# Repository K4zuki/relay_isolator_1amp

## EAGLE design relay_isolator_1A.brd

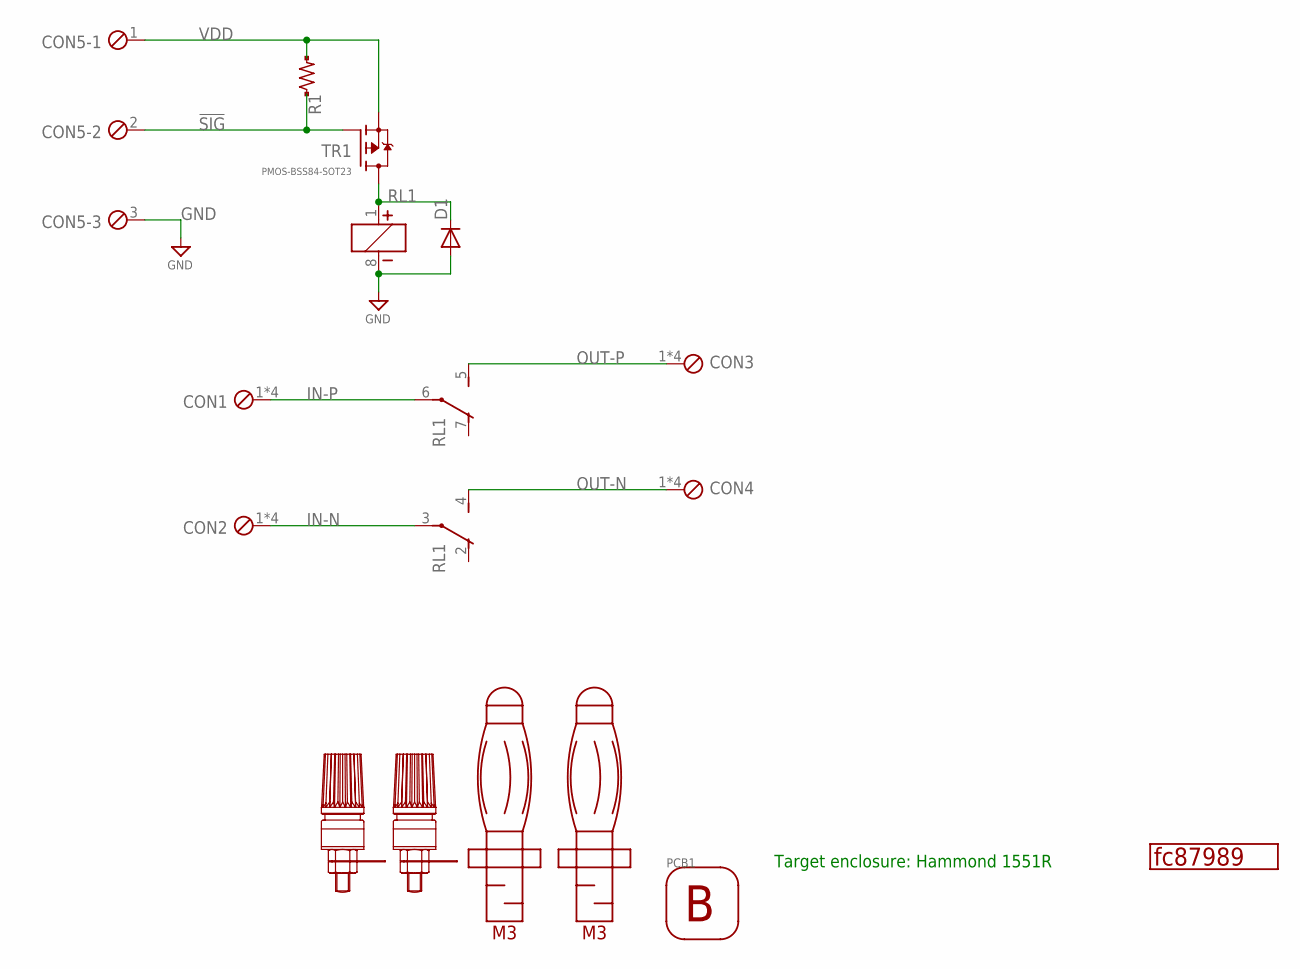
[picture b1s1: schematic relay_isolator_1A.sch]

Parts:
CON1, CON2: KEYSTONE-7790; KEYSTONE7790
CON3, CON4: KEYSTONE-7792; KEYSTONE7790
CON5: ETB43034B; ETB43034
D1: DIODE2-100V0.3A-SOD123; DIODE-2125
GIT1: fc87989; GIT-REVISION_1.7
PCB1: HAMMOND-PCB-BK-1551R; HAMMOND-1551R
R1: R-US-10K-1608; R-1608-PADPAD
REF1, REF2: POMONA72918
REF3, REF4: T-6530
RL1: RELAY-2C-POL-5V-G6K-2P; G6K-2P
TR1: PMOS-BSS84-SOT23; SOT95P300X140-3N

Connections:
!SIG!: CON5.2, R1.1, TR1.1 (G)
GND: CON5.3, D1.A, RL1.8 (2)
IN-N: CON2.1, CON2.2, CON2.3, CON2.4, RL1.3 (COM)
IN-P: CON1.1, CON1.2, CON1.3, CON1.4, RL1.6 (COM)
unnamed: D1.K (C), RL1.1, TR1.3 (D)
OUT-N: CON4.1, CON4.2, CON4.3, CON4.4, RL1.4 (NO)
OUT-P: CON3.1, CON3.2, CON3.3, CON3.4, RL1.5 (NO)
VDD: CON5.1, R1.2, TR1.2 (S)

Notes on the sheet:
Target enclosure: Hammond 1551R

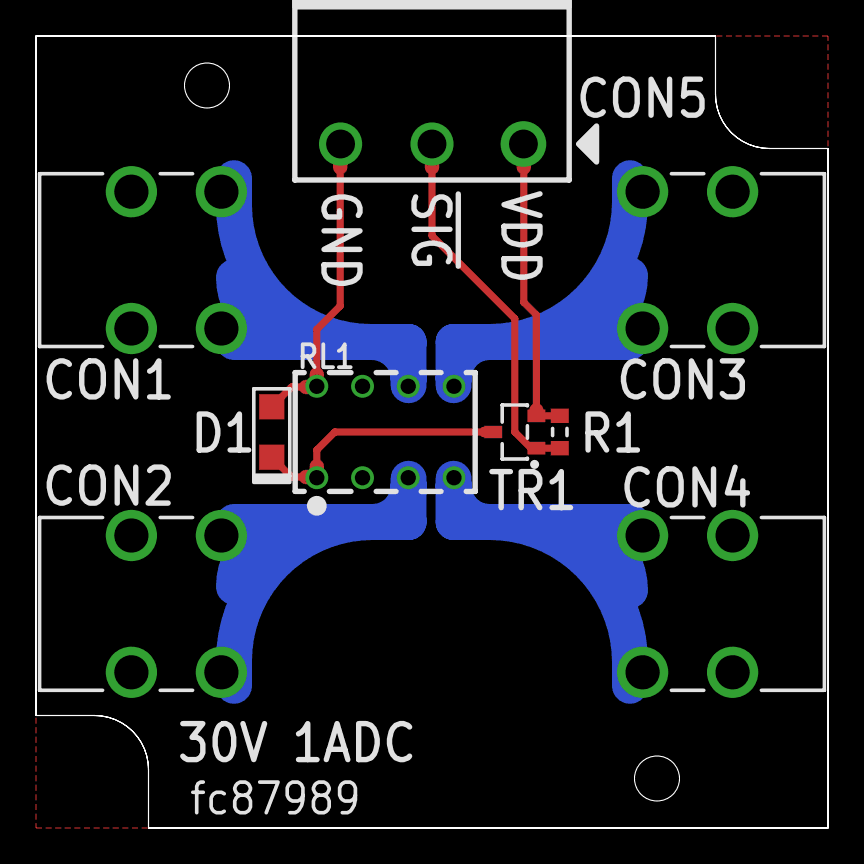
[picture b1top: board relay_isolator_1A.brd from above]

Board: 2 copper layers, 44.0 x 44.0 mm, 15 parts (0 on the bottom side), 8 nets.

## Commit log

2017-12-05 update git hash
2017-12-05 update layout and gerber
2017-12-05 MIT licensed
2017-12-06 update layout and library
2017-12-26 add T-6530 and POMONA72918 reference modules
    - update library
    - apply lib update for relay
    - update relay and diode traces
2017-12-26 all components on top mount
2017-12-26 prepare CI config
2017-12-26 bugfix ci config
2017-12-26 fix typo in ci config
2017-12-26 test ci config
2017-12-26 ci fixed
2018-01-06 clear unnecessary spin flag
2018-01-08 apply library update
